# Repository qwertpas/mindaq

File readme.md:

# mindaq PCB

A cheap and minimal data aquisition system for reading 6-axis force/torque sensors at high rates.

- 2.5V strain gauge excitation using precision reference (REF5025)
- Simultaneous sampling 24-bit ADC (ADS131M08) with 8 channels at 32k samples/second for
    - 6x strain gauges
    - 1x voltage up to 29.4V 
    - 1x current using external low-side shunt resistor
- Controlled by ESP32S3 Supermini dev board (USB-C powered)
- Display live force/torque data on Adafruit color TFT
- 42 x 29 mm board size
- 2-layer, single side components, JLCPCB economic assembly
- About $11 in parts cost per board (including ESP32S3)
- Single order of 2pcs is $70, 5pcs is $120 including everything (shipping and customs about doubles the cost!)

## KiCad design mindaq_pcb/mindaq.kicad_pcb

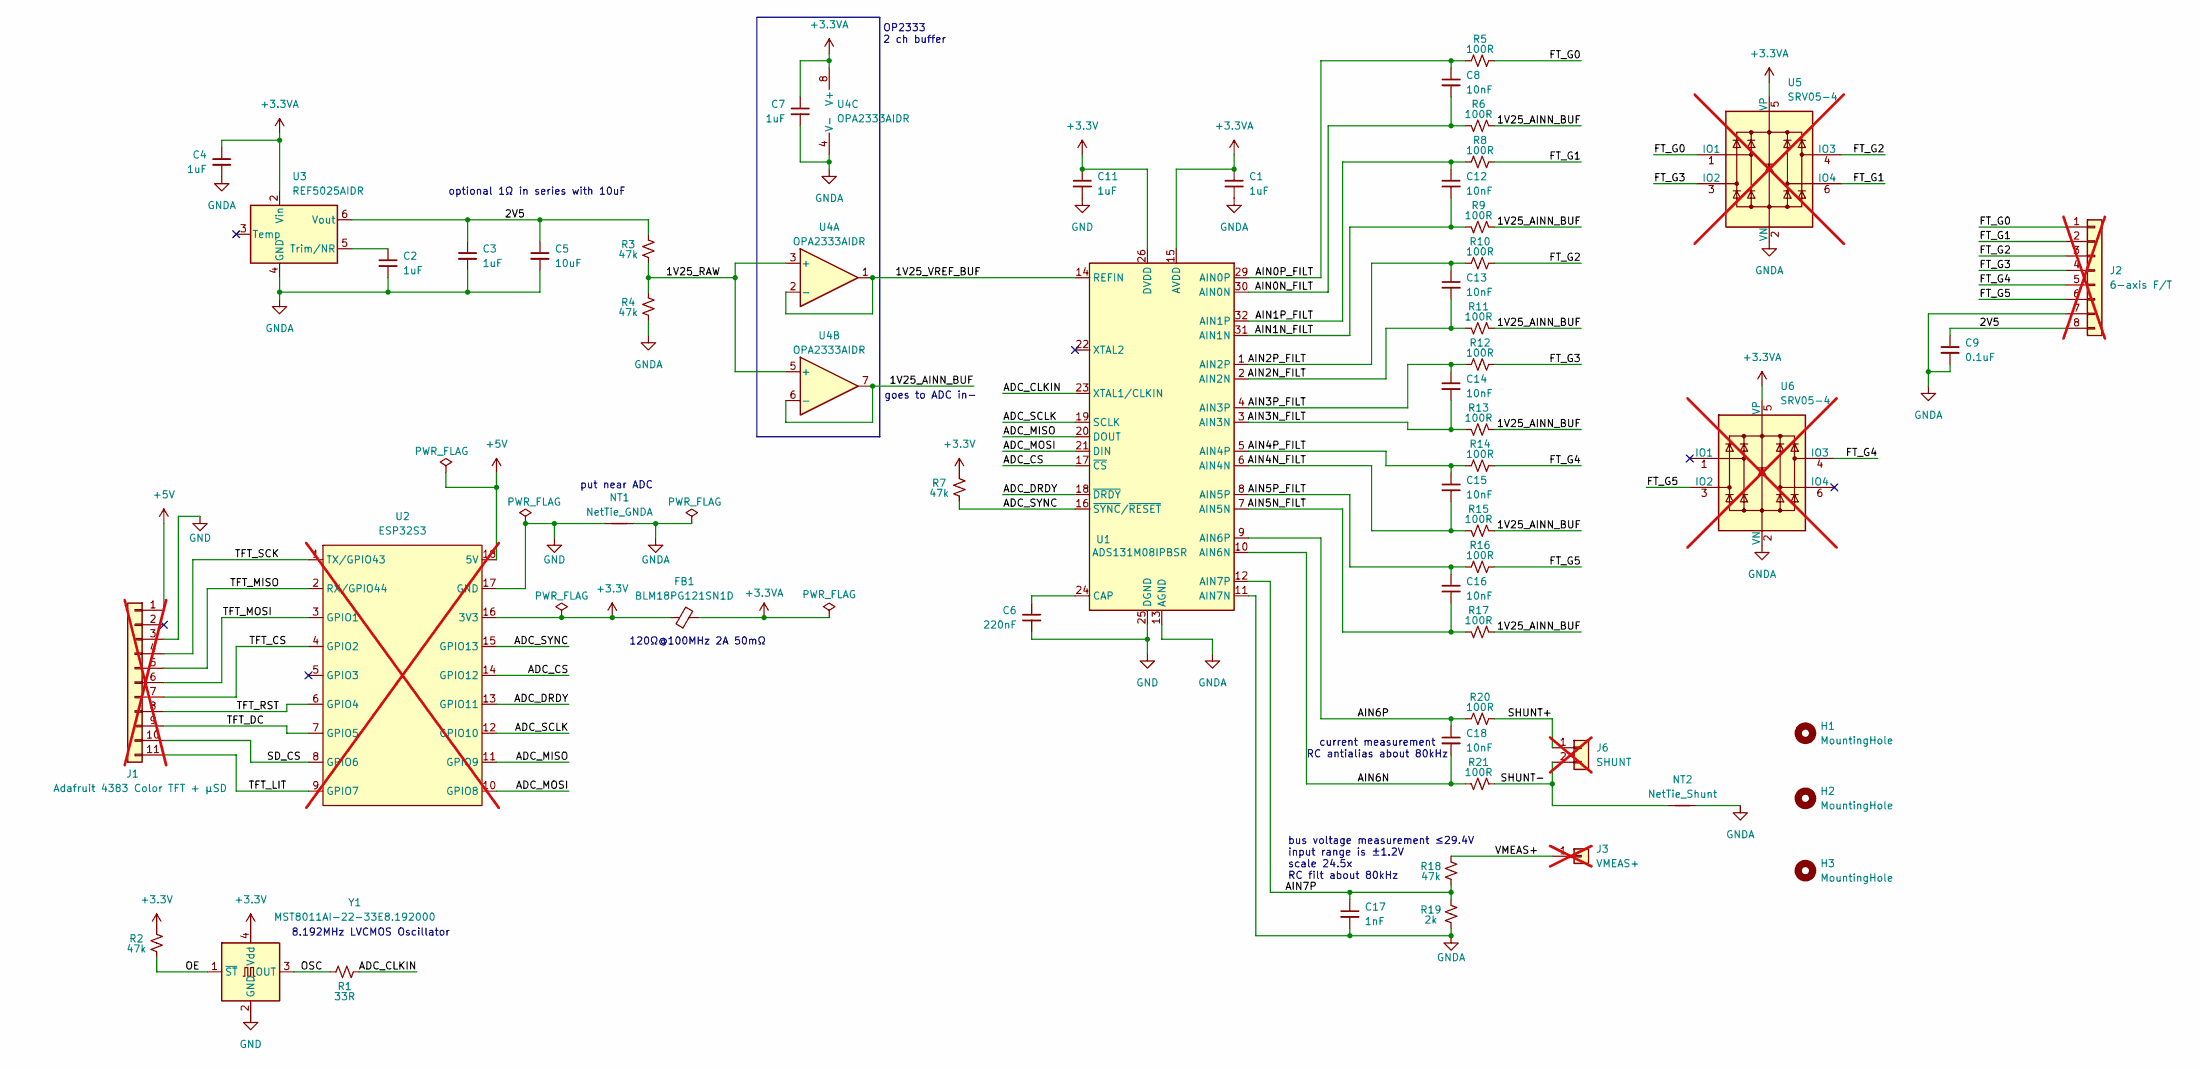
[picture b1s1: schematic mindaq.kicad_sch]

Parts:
C1, C2, C3, C4, C7, C11: 1uF; C_0402_1005Metric; LCSC C52923
C5: 10uF; C_0402_1005Metric; LCSC C15525
C6: 220nF; C_0402_1005Metric; LCSC C16772
C8, C12, C13, C14, C15, C16, C18: 10nF; C_0402_1005Metric; LCSC C15195
C9: 0.1uF; C_0402_1005Metric; LCSC C307331
C17: 1nF; C_0402_1005Metric; LCSC C1523
FB1: BLM18PG121SN1D; L_0603_1608Metric; LCSC C14709
H1, H2, H3: MountingHole; MountingHole_2.2mm_M2
J1: Adafruit 4383 Color TFT + μSD; PinSocket_1x11_P2.54mm_Vertical; not fitted
J2: 6-axis F/T; PinSocket_1x08_P2.54mm_Vertical; not fitted
J3: VMEAS+; PinSocket_1x01_P2.54mm_Vertical; not fitted
J6: SHUNT; PinSocket_1x02_P2.54mm_Vertical; not fitted
NT1: NetTie_GNDA; NetTie-2_SMD_Pad2.0mm
NT2: NetTie_Shunt; NetTie-2_SMD_Pad0.5mm
R1: 33R; R_0402_1005Metric; LCSC C25105
R2, R3, R4, R7, R18: 47k; R_0402_1005Metric; LCSC C25792
R5, R6, R8, R9, R10, R11, R12, R13, R14, R15, R16, R17, R20, R21: 100R; R_0402_1005Metric; LCSC C25076
R19: 2k; R_0402_1005Metric; LCSC C4109
U1: ADS131M08IPBSR; TQFP-32_5x5mm_P0.5mm; LCSC C2862610
U2: ESP32S3; esp32s3-supermini; not fitted
U3: REF5025AIDR; SOIC-8_3.9x4.9mm_P1.27mm; LCSC C11341
U4: OPA2333AIDR; SOIC-8_3.9x4.9mm_P1.27mm; LCSC C38732
U5, U6: SRV05-4; SOT-23-6; LCSC C20615829; not fitted
Y1: MST8011AI-22-33E8.192000; Crystal_SMD_3225-4Pin_3.2x2.5mm; LCSC C51026284

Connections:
+3.3V: C11.1, FB1.1, R2.1, R7.1, U1.26 (DVDD), U2.16 (3V3), Y1.4 (Vdd)
+3.3VA: C1.1, C4.1, C7.1, FB1.2, U1.15 (AVDD), U3.2 (Vin), U4.8 (V+), U5.5 (VP), U6.5 (VP)
+5V: J1.1, U2.18 (5V)
/1V25_AINN_BUF: R6.2, R9.2, R11.2, R13.2, R15.2, R17.2, U4.6 (-), U4.7
/1V25_RAW: R3.2, R4.1, U4.3 (+), U4.5 (+)
/1V25_VREF_BUF: U1.14 (REFIN), U4.1, U4.2 (-)
/2V5: C3.1, C5.1, C9.1, J2.8, R3.1, U3.6 (Vout)
/ADC_CLKIN: R1.1, U1.23 (XTAL1/CLKIN)
/ADC_CS: U1.17 (~CS), U2.14 (GPIO12)
/ADC_DRDY: U1.18 (~DRDY), U2.13 (GPIO11)
/ADC_MISO: U1.20 (DOUT), U2.11 (GPIO9)
/ADC_MOSI: U1.21 (DIN), U2.10 (GPIO8)
/ADC_SCLK: U1.19 (SCLK), U2.12 (GPIO10)
/ADC_SYNC: R7.2, U1.16 (~SYNC/~RESET), U2.15 (GPIO13)
/AIN0N_FILT: C8.2, R6.1, U1.30 (AIN0N)
/AIN0P_FILT: C8.1, R5.1, U1.29 (AIN0P)
/AIN1N_FILT: C12.2, R9.1, U1.31 (AIN1N)
/AIN1P_FILT: C12.1, R8.1, U1.32 (AIN1P)
/AIN2N_FILT: C13.2, R11.1, U1.2 (AIN2N)
/AIN2P_FILT: C13.1, R10.1, U1.1 (AIN2P)
/AIN3N_FILT: C14.2, R13.1, U1.3 (AIN3N)
/AIN3P_FILT: C14.1, R12.1, U1.4 (AIN3P)
/AIN4N_FILT: C15.2, R15.1, U1.6 (AIN4N)
/AIN4P_FILT: C15.1, R14.1, U1.5 (AIN4P)
/AIN5N_FILT: C16.2, R17.1, U1.7 (AIN5N)
/AIN5P_FILT: C16.1, R16.1, U1.8 (AIN5P)
/AIN6N: C18.2, R21.1, U1.10 (AIN6N)
/AIN6P: C18.1, R20.1, U1.9 (AIN6P)
/AIN7P: C17.1, R18.2, R19.1, U1.12 (AIN7P)
/FT_G0: J2.1, R5.2, U5.1 (IO1)
/FT_G1: J2.2, R8.2, U5.6 (IO4)
/FT_G2: J2.3, R10.2, U5.4 (IO3)
/FT_G3: J2.4, R12.2, U5.3 (IO2)
/FT_G4: J2.5, R14.2, U6.4 (IO3)
/FT_G5: J2.6, R16.2, U6.3 (IO2)
/OE: R2.2, Y1.1 (~ST)
/OSC: R1.2, Y1.3 (OUT)
/SD_CS: J1.10, U2.8 (GPIO6)
/SHUNT+: J6.1, R20.2
/SHUNT-: J6.2, NT2.1, R21.2
/TFT_CS: J1.7, U2.4 (GPIO2)
/TFT_DC: J1.9, U2.7 (GPIO5)
/TFT_LIT: J1.11, U2.9 (GPIO7)
/TFT_MISO: J1.5, U2.2 (RX/GPIO44)
/TFT_MOSI: J1.6, U2.3 (GPIO1)
/TFT_RST: J1.8, U2.6 (GPIO4)
/TFT_SCK: J1.4, U2.1 (TX/GPIO43)
/VMEAS+: J3.1 (Pin_1_1), R18.1
GND: C6.2, C11.2, J1.3, NT1.1, U1.25 (DGND), U2.17 (GND), Y1.2 (GND)
GNDA: C1.2, C2.2, C3.2, C4.2, C5.2, C7.2, C9.2, C17.2, J2.7, NT1.2, NT2.2, R4.2, R19.2, U1.11 (AIN7N), U1.13 (AGND), U1.27 (AGND), U1.28 (AGND), U3.4 (GND), U4.4 (V-), U5.2 (VN), U6.2 (VN)
unnamed: C6.1, U1.24 (CAP)
unnamed: C2.1, U3.5 (Trim/NR)

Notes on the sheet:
OP2333 2 ch buffer
current measurement RC antialias about 80kHz
bus voltage measurement ≤29.4V input range is ±1.2V scale 24.5x RC filt about 80kHz
120Ω@100MHz 2A 50mΩ
goes to ADC in-
optional 1Ω in series with 10uF
put near ADC
8.192MHz LVCMOS Oscillator

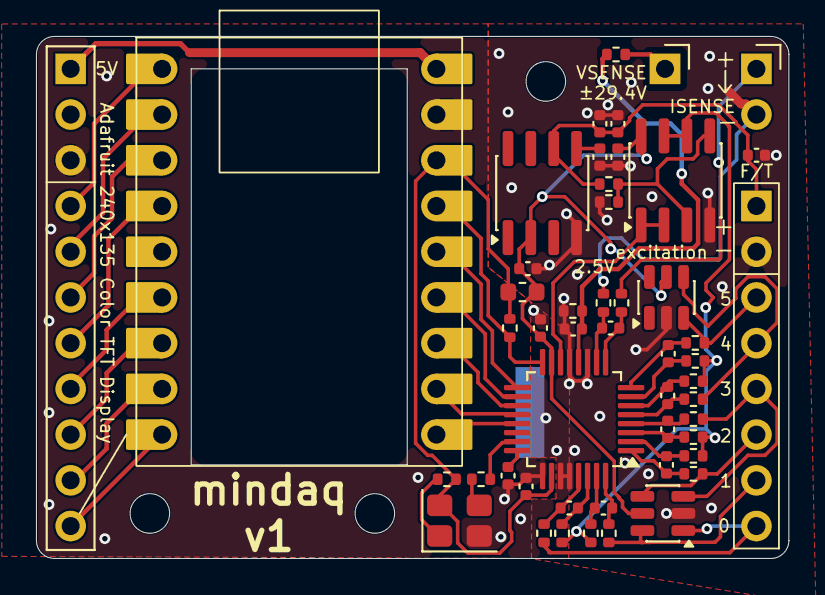
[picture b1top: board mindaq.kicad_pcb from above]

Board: 2 copper layers, 41.8 x 29.0 mm, 55 parts (1 on the bottom side), 52 nets.

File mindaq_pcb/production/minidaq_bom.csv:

Designator,Footprint,Quantity,Value,LCSC Part #
"C1, C11, C2, C3, C4, C7",0402,6,1uF,C52923
"C12, C13, C14, C15, C16, C18, C8",0402,7,10nF,C15195
C17,0402,1,1nF,C1523
C5,0402,1,10uF,C15525
C6,0402,1,220nF,C16772
C9,0402,1,0.1uF,C307331
FB1,0603,1,BLM18PG121SN1D,C14709
R1,0402,1,33R,C25105
"R10, R11, R12, R13, R14, R15, R16, R17, R20, R21, R5, R6, R8, R9",0402,14,100R,C25076
"R18, R2, R3, R4, R7",0402,5,47k,C25792
R19,0402,1,2k,C4109
U1,TQFP-32_5x5mm_P0.5mm,1,ADS131M08IPBSR,C2862610
U3,SOIC-8_3.9x4.9mm_P1.27mm,1,REF5025AIDR,C11341
U4,SOIC-8_3.9x4.9mm_P1.27mm,1,OPA2333AIDR,C38732
Y1,Crystal_SMD_3225-4Pin_3.2x2.5mm,1,MST8011AI-22-33E8.192000,C51026284

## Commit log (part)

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2026-04-02 generate production files for jlcpcb
2026-04-02 readme update with price
2026-04-15 mindaq fw and gui works with rough mapping
2026-04-15 tft display
2026-04-20 FT8978 calibration
2026-04-20 use 6x6 factory calibration for FT8978
2026-05-06 before trying searched mapping
2026-05-06 try 32ksps adc read and stream
2026-05-06 32sps gui save
2026-05-06 works with fitted Fz
2026-05-06 clean up mapping
2026-05-07 calibrated and adjustabl gain
2026-05-24 add the whole gain range, raw adc streaming
2026-05-24 reorg scripts, finish up capture gui
2026-05-24 update readme and docs for capture gui
2026-05-24 remove .vscode
2026-05-24 update capture readme
2026-05-24 fix download link
2026-05-24 update download link
2026-05-24 update readme with adc+- and gain setting
2026-05-24 clean up windows py -3
